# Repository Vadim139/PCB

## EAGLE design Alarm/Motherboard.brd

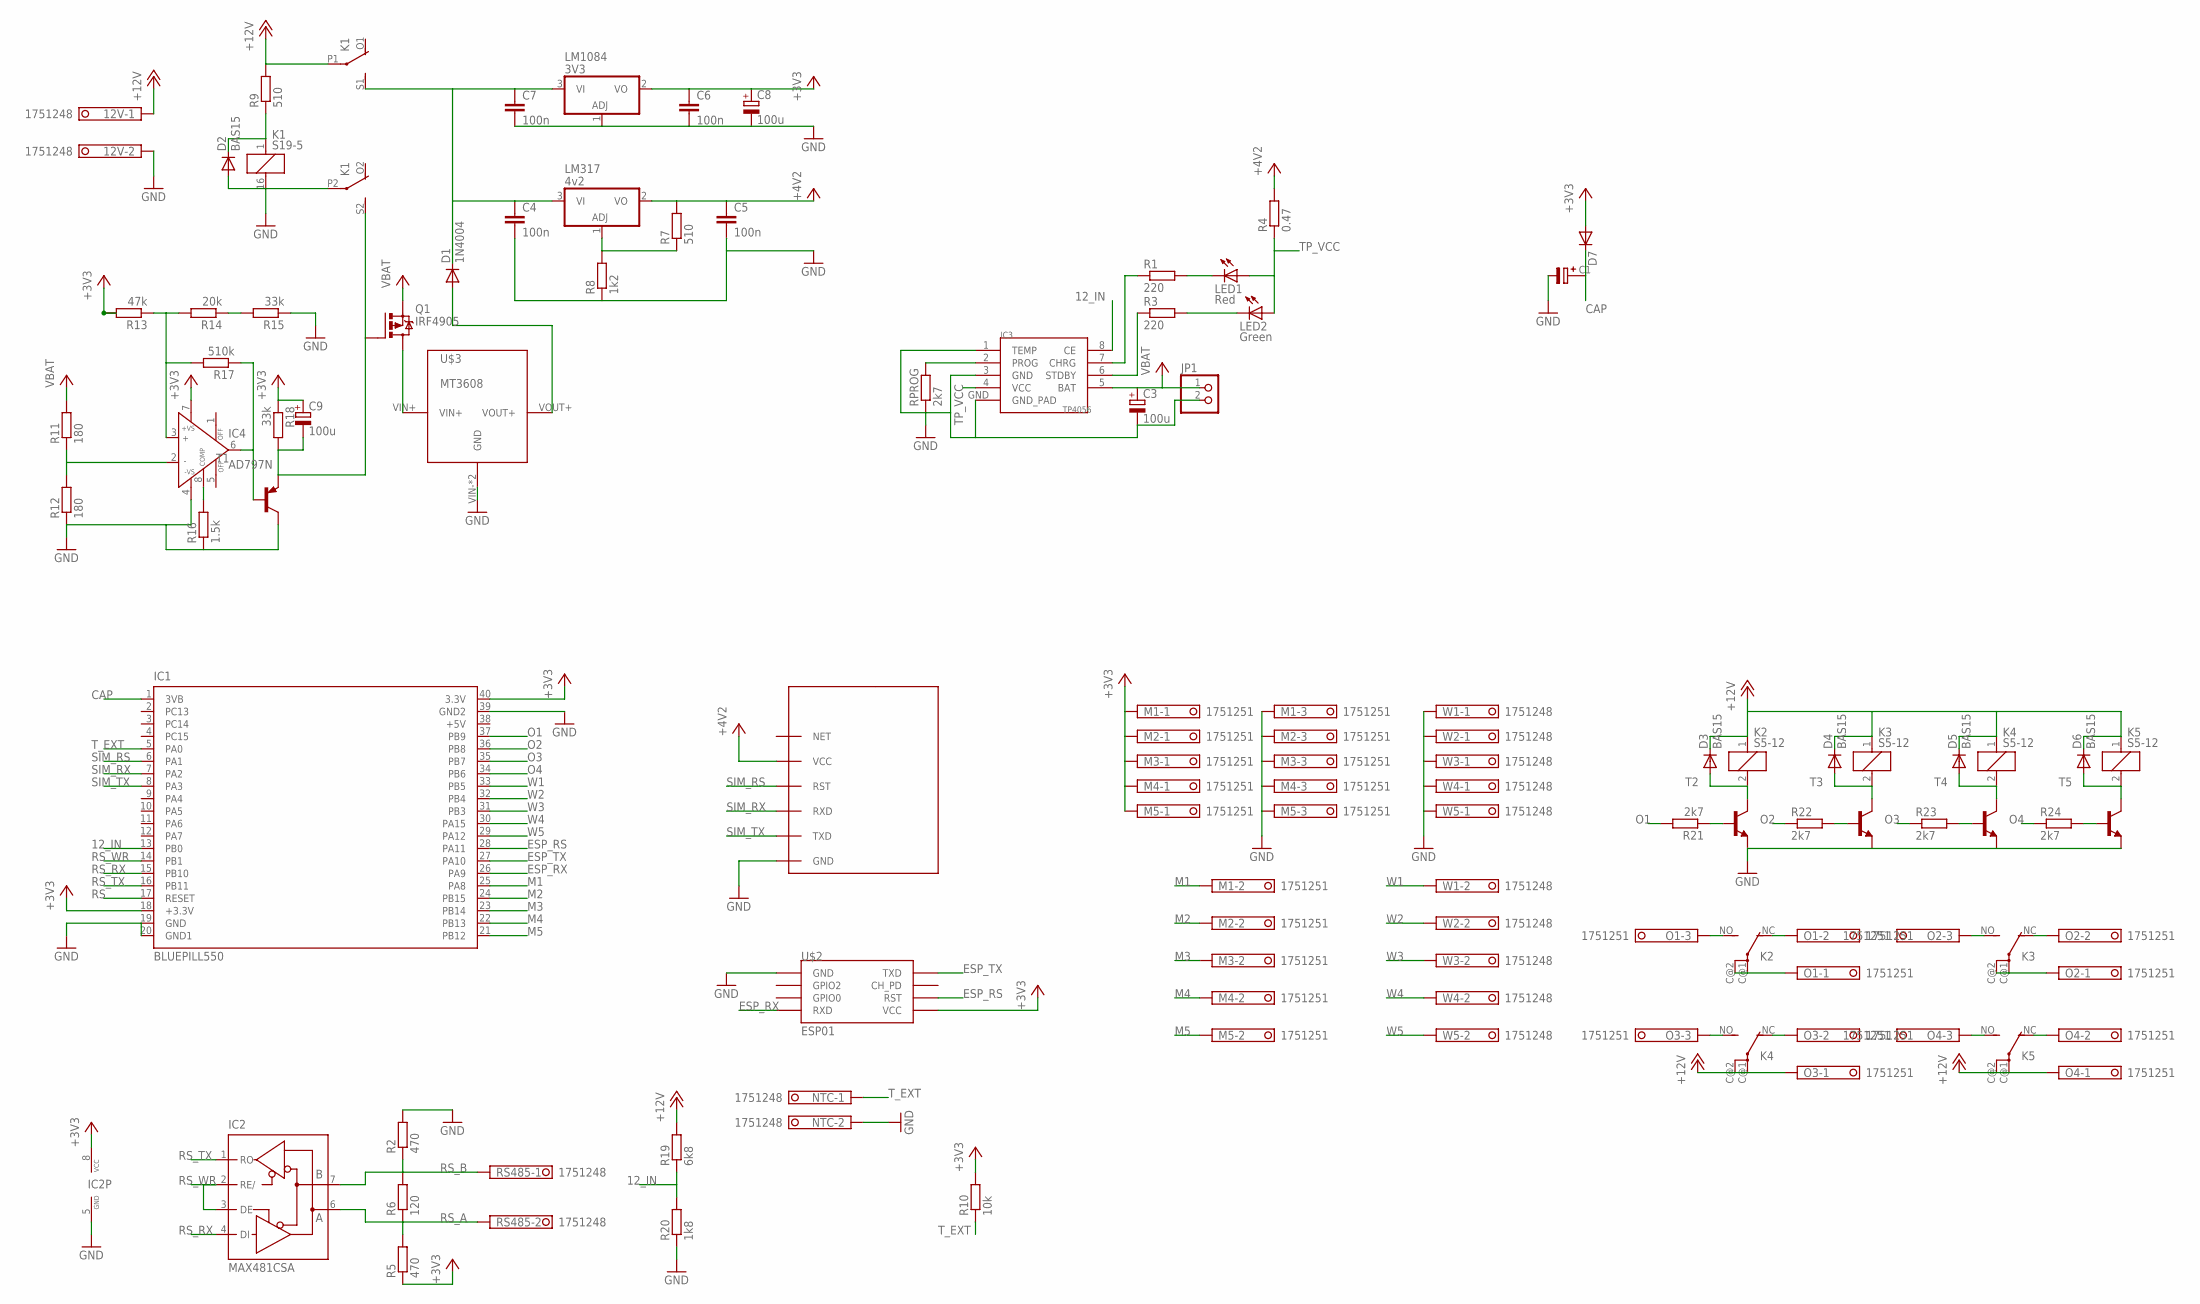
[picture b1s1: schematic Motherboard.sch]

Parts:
12V: 1751248
C1: CAP-13,5; PAC-G-1
C3, C8, C9: 100u; E2,5-6E
C4, C5, C6, C7: 100n; C2012
D1: 1N4004; DO41-10
D2, D3, D4, D5, D6, D7: BAS15; DO34-7
IC1: BLUEPILL550; DIL40
IC2: MAX481CSA; SO08
IC3: TP4056; SOP-8
IC4: AD797N; DIL08
JP1: PINHD-1X2; 1X02
K1: S19-5; 351
K2, K3, K4, K5: S5-12; HY
LED1: Red; CHIP-LED0805
LED2: Green; CHIP-LED0805
LM317: 4v2; TO220H
LM1084: 3V3; TO220H
M1, M2, M3, M4, M5: 1751251
NTC: 1751248
O1, O2, O3, O4: 1751251
Q1: IRF4905; TO220BH
R1, R3: 220; R0805
R2, R5: 470; 0204/5
R4: 0.47; 0207/12
R6: 120; 0204/7
R7, R9: 510; 0204/7
R8: 1k2; 0204/7
R10: 10k; 0204/5
R11, R12: 180; 0204/7
R13: 47k; 0204/7
R14: 20k; 0204/7
R15, R18: 33k; 0204/7
R16: 1.5k; 0204/7
R17: 510k; 0204/7
R19: 6k8; 0204/5
R20: 1k8; 0204/5
R21, R22, R23, R24: 2k7; 0204/7
RPROG: 2k7; 0204/7
RS485: 1751248
T1: BC327-40-PNP-TO92-EBC; TO92-EBC
T2, T3, T4, T5: -NPN-TO92-ECB; TO92-ECB
U$1: SIM800L; SIM-CORE
U$2: ESP01
U$3: MT3608
W1, W2, W3, W4, W5: 1751248

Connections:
4V2: C5.1, LM317.2 (VO), R4.2, R7.2, U$1.VCC
12_IN: IC1.13 (PB0), IC3.8 (CE), R19.1, R20.2
+3V3: C6.1, C8.+, C9.+, D7.A, IC1.18 (+3.3V), IC1.40 (3.3V), IC2.8 (VCC), IC4.7 (+VS), LM1084.2 (VO), M1.1, M2.1, M3.1, M4.1, M5.1, R5.1, R10.2, R13.2, R18.1, U$2.VCC
+12V: 12V.1, D3.C, D4.C, D5.C, D6.C, K1.P1, K2.1, K3.1, K4.1, K4.C@1, K4.C@2, K5.1, K5.C@1, K5.C@2, O3.1, O4.1, R9.2, R19.2
CAP: C1.+, D7.C, IC1.1 (3VB)
ESP_RS: IC1.28 (PA11), U$2.RST
ESP_RX: IC1.26 (PA9), U$2.RX (RXD)
ESP_TX: IC1.27 (PA10), U$2.TX (TXD)
GND: 12V.2, C1.-, C3.-, C4.2, C5.2, C6.2, C7.2, C8.-, D2.A, IC1.19 (GND), IC1.20 (GND1), IC1.39 (GND2), IC2.5 (GND), IC3.1 (TEMP), IC3.3 (GND), IC3.GND (GND_PAD), IC4.4 (-VS), JP1.2, K1.16 (2), K1.P2, LM1084.1 (ADJ), M1.3, M2.3, M3.3, M4.3, M5.3, NTC.2, R2.2, R8.1, R12.1, R15.1, R16.1, R20.1, RPROG.1, T1.C, T2.E, T3.E, T4.E, T5.E, U$1.GND, U$2.GND, U$3.VIN- (GND), U$3.VOUT- (GND), W1.1, W2.1, W3.1, W4.1, W5.1
M1: IC1.25 (PA8), M1.2
M2: IC1.24 (PB15), M2.2
M3: IC1.23 (PB14), M3.2
M4: IC1.22 (PB13), M4.2
M5: IC1.21 (PB12), M5.2
unnamed: IC3.2 (PROG), RPROG.2
unnamed: D2.C, K1.1, R9.1
unnamed: LED1.C, R1.2
unnamed: LED2.C, R3.2
unnamed: IC3.7 (CHRG), R1.1
unnamed: IC3.6 (STDBY), R3.1
unnamed: C4.1, C7.1, D1.C, K1.S1 (S), LM317.3 (VI), LM1084.3 (VI)
unnamed: Q1.D, U$3.VIN+
unnamed: IC4.3 (IN+), R13.1, R14.2, R17.2
unnamed: IC4.2 (IN-), R11.1, R12.2
unnamed: IC4.8 (COMP), R16.2
unnamed: IC4.6 (OUT), R17.1, T1.B
unnamed: LM317.1 (ADJ), R7.1, R8.2
unnamed: C9.-, K1.S2 (S), Q1.G, R18.2, T1.E
unnamed: R24.2, T5.B
unnamed: R23.2, T4.B
unnamed: R22.2, T3.B
unnamed: R21.1, T2.B
unnamed: K4.NO (S), O3.3
unnamed: K4.NC (O), O3.2
unnamed: K5.NO (S), O4.3
unnamed: K5.NC (O), O4.2
unnamed: K2.NO (S), O1.3
unnamed: K2.C@1, K2.C@2, O1.1
unnamed: K2.NC (O), O1.2
unnamed: K3.NO (S), O2.3
unnamed: K3.NC (O), O2.2
unnamed: K3.C@1, K3.C@2, O2.1
unnamed: R14.1, R15.2
unnamed: D6.A, K5.2, T5.C
unnamed: D3.A, K2.2, T2.C
unnamed: D4.A, K3.2, T3.C
unnamed: D5.A, K4.2, T4.C
O1: IC1.37 (PB9), R21.2
O2: IC1.36 (PB8), R22.1
O3: IC1.35 (PB7), R23.1
O4: IC1.34 (PB6), R24.1
PA6: IC1.11 (PA6)
PA7: IC1.12 (PA7)
RS: IC1.17 (RESET)
RS_A: IC2.6 (A), R5.2, R6.1, RS485.2
RS_B: IC2.7 (B), R2.1, R6.2, RS485.1
RS_RX: IC1.15 (PB10), IC2.4 (DI)
RS_TX: IC1.16 (PB11), IC2.1 (RO)
RS_WR: IC1.14 (PB1), IC2.2 (RE/), IC2.3 (DE)
SIM_RS: IC1.6 (PA1), U$1.RST
SIM_RX: IC1.7 (PA2), U$1.RXD
SIM_TX: IC1.8 (PA3), U$1.TXD
TP_VCC: IC3.4 (VCC), LED1.A, LED2.A, R4.1
T_EXT: IC1.5 (PA0), NTC.1, R10.1
VBAT: C3.+, IC3.5 (BAT), JP1.1, Q1.S, R11.2
VOUT+: D1.A, U$3.VOUT+
W1: IC1.33 (PB5), W1.2
W2: IC1.32 (PB4), W2.2
W3: IC1.31 (PB3), W3.2
W4: IC1.30 (PA15), W4.2
W5: IC1.29 (PA12), W5.2

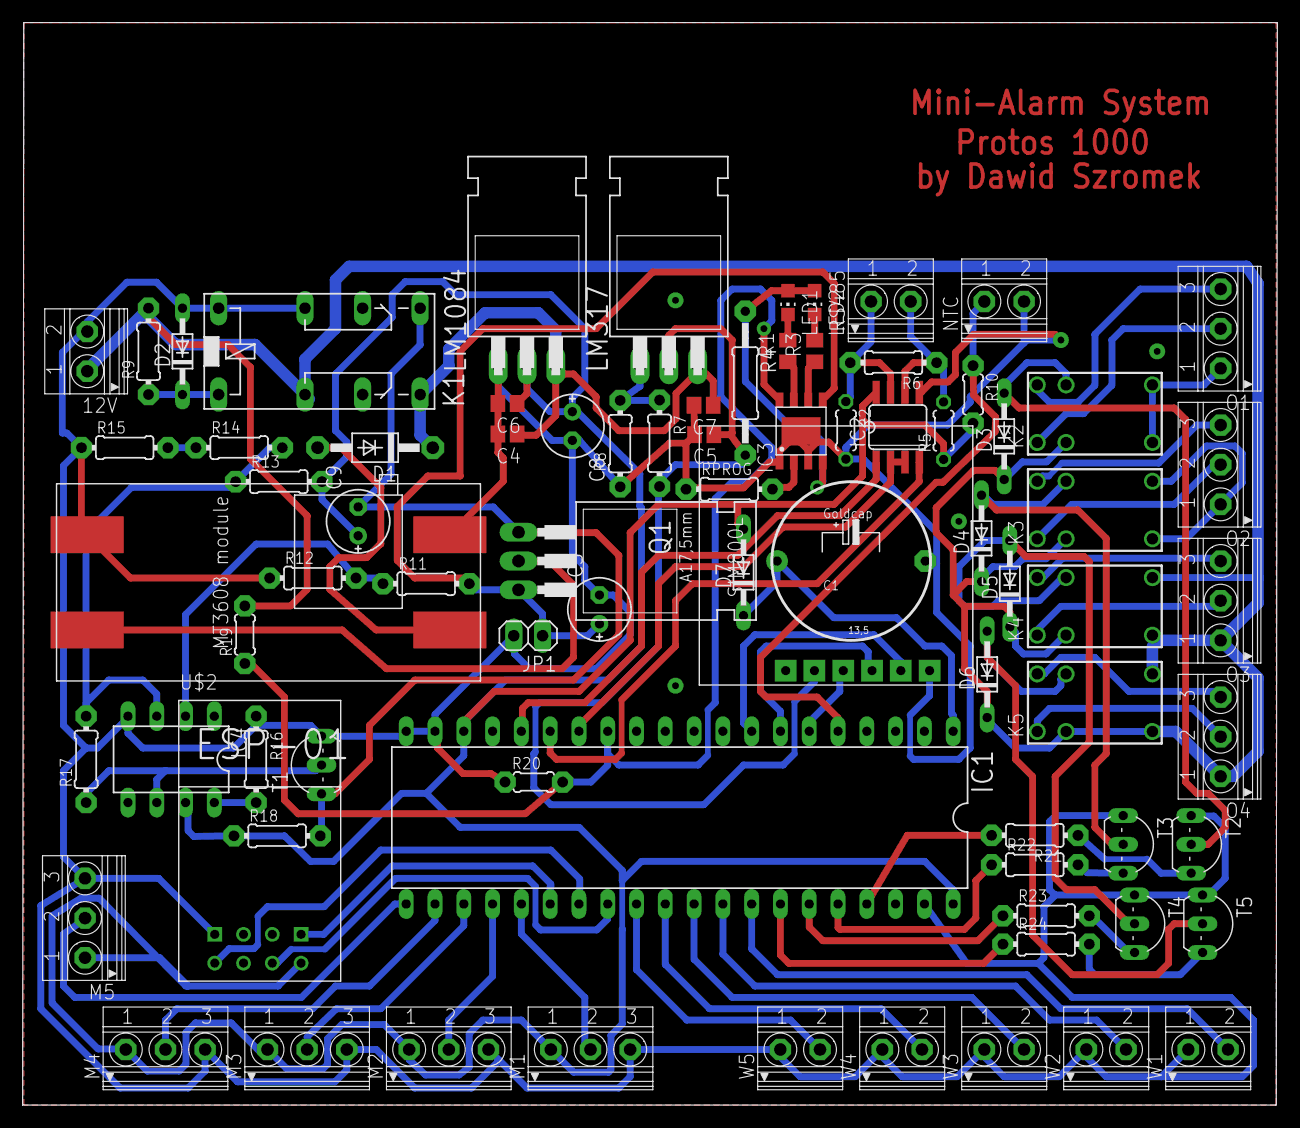
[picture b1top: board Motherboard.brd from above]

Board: 2 copper layers, 110.7 x 95.5 mm, 80 parts (0 on the bottom side), 68 nets.

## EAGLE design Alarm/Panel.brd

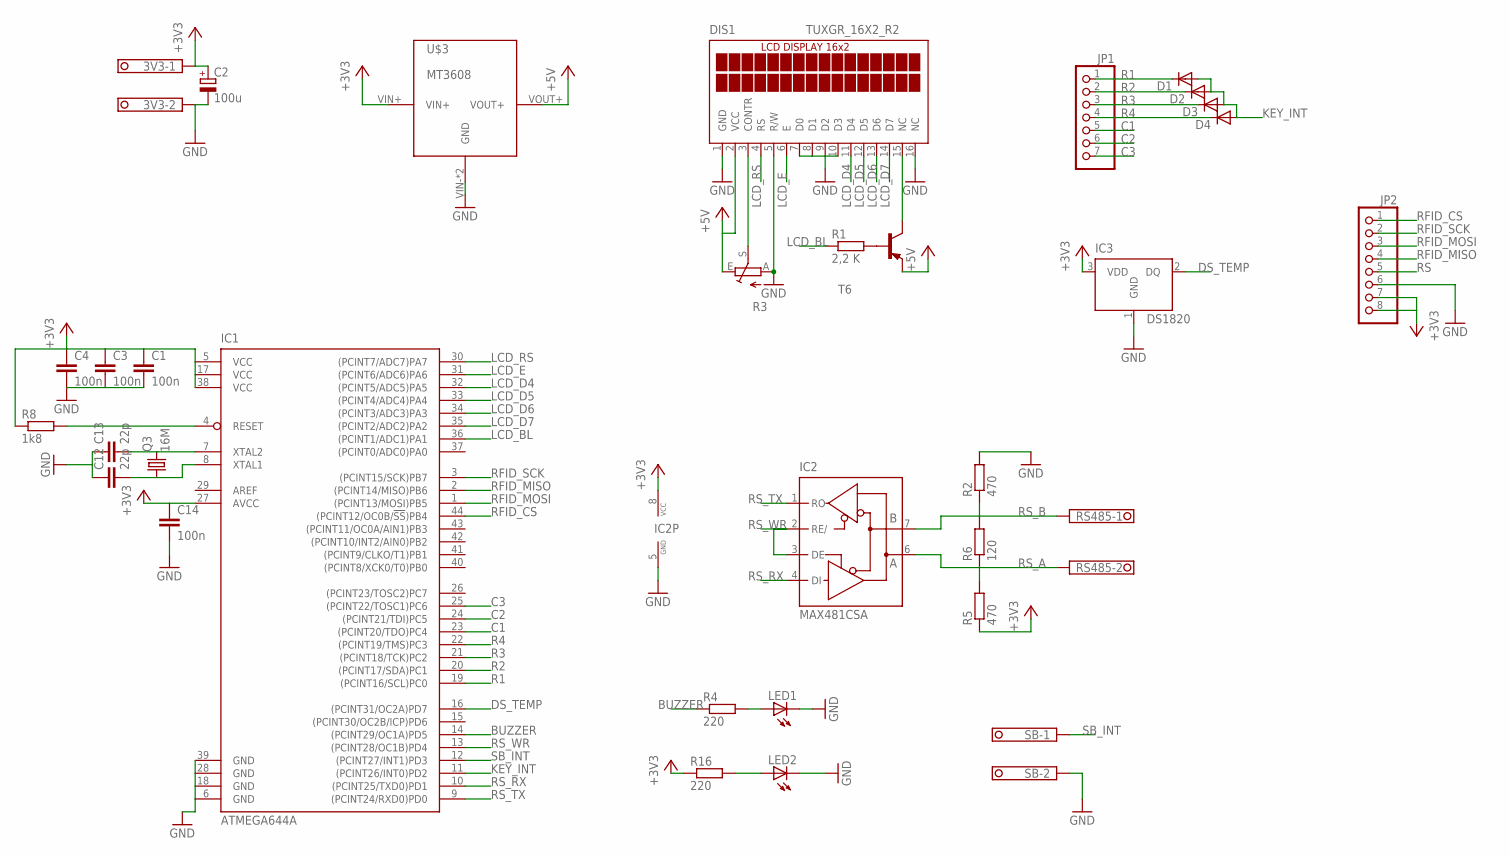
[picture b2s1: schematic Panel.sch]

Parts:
3V3: 1751248
C1, C3, C4, C14: 100n; C2012
C2: 100u; E2,5-6E
C12, C13: 22p; C050-024X044
D1, D2, D3, D4: BAS15; DO34-7
DIS1: TUXGR_16X2_R2
IC1: ATMEGA644A; TQFP44
IC2: MAX481CSA; SO08
IC3: DS1820; TO-92-
JP1: PINHD-1X7; 1X07
JP2: PINHD-1X8; 1X08
LED1, LED2: LED3MM
Q3: 16M; HC49U-V
R1: 2,2 K; 0204/7
R2, R5: 470; 0204/5
R3: TRIM_EU-CA6V; CA6V
R4, R16: 220; 0204/7
R6: 120; 0204/7
R8: 1k8; 0204/7
RS485: 1751248
SB: 1751248
T6: BC327-40-PNP-TO92-EBC; TO92-EBC
U$3: MT3608

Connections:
+3V3: 3V3.1, C1.1, C2.+, C3.1, C4.1, C14.1, IC1.5 (VCC), IC1.17 (VCC), IC1.27 (AVCC), IC1.38 (VCC), IC2.8 (VCC), IC3.3 (VDD), JP2.7, JP2.8, R5.1, R8.1, R16.1, U$3.VIN+
+5V: DIS1.2 (VCC), R3.E, T6.E, U$3.VOUT+
BUZZER: IC1.14 ((PCINT29/OC1A)PD5), R4.1
C1: IC1.23 ((PCINT20/TDO)PC4), JP1.5
C2: IC1.24 ((PCINT21/TDI)PC5), JP1.6
C3: IC1.25 ((PCINT22/TOSC1)PC6), JP1.7
DS_TEMP: IC1.16 ((PCINT31/OC2A)PD7), IC3.2 (DQ)
GND: 3V3.2, C1.2, C2.-, C3.2, C4.2, C12.1, C13.1, C14.2, DIS1.1 (GND), DIS1.5 (R/W), DIS1.7 (D0), DIS1.8 (D1), DIS1.9 (D2), DIS1.10 (D3), DIS1.16 (NC), IC1.6 (GND), IC1.18 (GND), IC1.28 (GND), IC1.39 (GND), IC2.5 (GND), IC3.1 (GND), JP2.6, LED1.K (C), LED2.K (C), R2.2, R3.A, SB.2, U$3.VIN- (GND), U$3.VOUT- (GND)
KEY_INT: D1.A, D2.A, D3.A, D4.A, IC1.11 ((PCINT26/INT0)PD2)
LCD_BL: IC1.36 ((PCINT1/ADC1)PA1), R1.1
LCD_D4: DIS1.11 (D4), IC1.32 ((PCINT5/ADC5)PA5)
LCD_D5: DIS1.12 (D5), IC1.33 ((PCINT4/ADC4)PA4)
LCD_D6: DIS1.13 (D6), IC1.34 ((PCINT3/ADC3)PA3)
LCD_D7: DIS1.14 (D7), IC1.35 ((PCINT2/ADC2)PA2)
LCD_E: DIS1.6 (E), IC1.31 ((PCINT6/ADC6)PA6)
LCD_RS: DIS1.4 (RS), IC1.30 ((PCINT7/ADC7)PA7)
unnamed: C12.2, IC1.8 (XTAL1), Q3.1
unnamed: R1.2, T6.B
unnamed: LED1.A, R4.2
unnamed: C13.2, IC1.7 (XTAL2), Q3.2
unnamed: DIS1.3 (CONTR), R3.S
unnamed: DIS1.15 (NC), T6.C
unnamed: LED2.A, R16.2
R1: D1.C, IC1.19 ((PCINT16/SCL)PC0), JP1.1
R2: D2.C, IC1.20 ((PCINT17/SDA)PC1), JP1.2
R3: D3.C, IC1.21 ((PCINT18/TCK)PC2), JP1.3
R4: D4.C, IC1.22 ((PCINT19/TMS)PC3), JP1.4
RFID_CS: IC1.44 ((PCINT12/OC0B/!SS!)PB4), JP2.1
RFID_MISO: IC1.2 ((PCINT14/MISO)PB6), JP2.4
RFID_MOSI: IC1.1 ((PCINT13/MOSI)PB5), JP2.3
RFID_SCK: IC1.3 ((PCINT15/SCK)PB7), JP2.2
RS: IC1.4 (RESET), JP2.5, R8.2
RS_A: IC2.6 (A), R5.2, R6.1, RS485.2
RS_B: IC2.7 (B), R2.1, R6.2, RS485.1
RS_RX: IC1.10 ((PCINT25/TXD0)PD1), IC2.4 (DI)
RS_TX: IC1.9 ((PCINT24/RXD0)PD0), IC2.1 (RO)
RS_WR: IC1.13 ((PCINT28/OC1B)PD4), IC2.2 (RE/), IC2.3 (DE)
SB_INT: IC1.12 ((PCINT27/INT1)PD3), SB.1

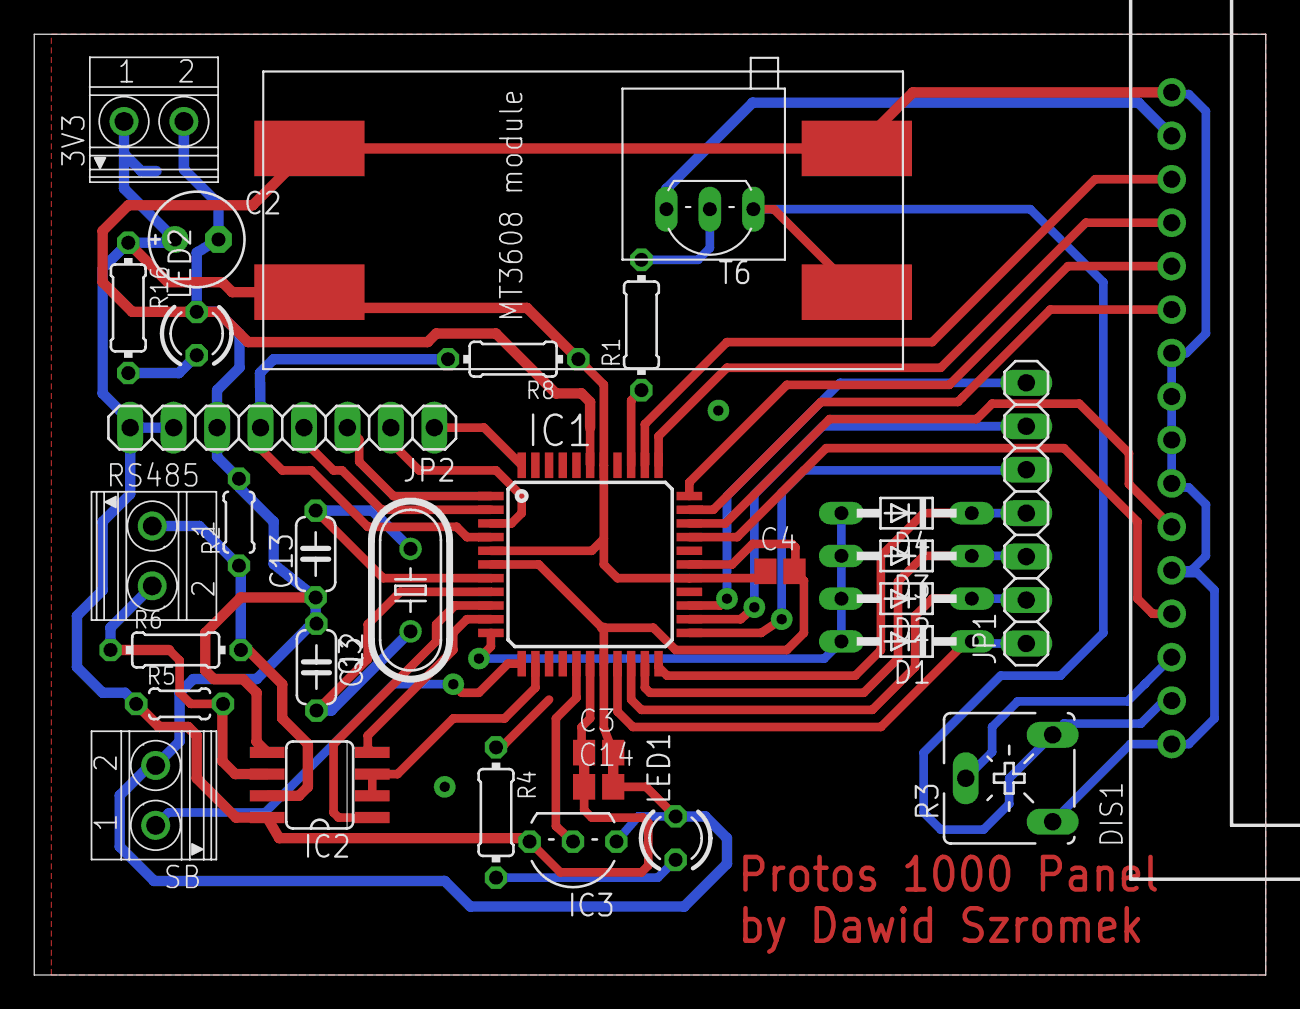
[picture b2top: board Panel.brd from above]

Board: 2 copper layers, 72.0 x 55.0 mm, 33 parts (1 on the bottom side), 38 nets.

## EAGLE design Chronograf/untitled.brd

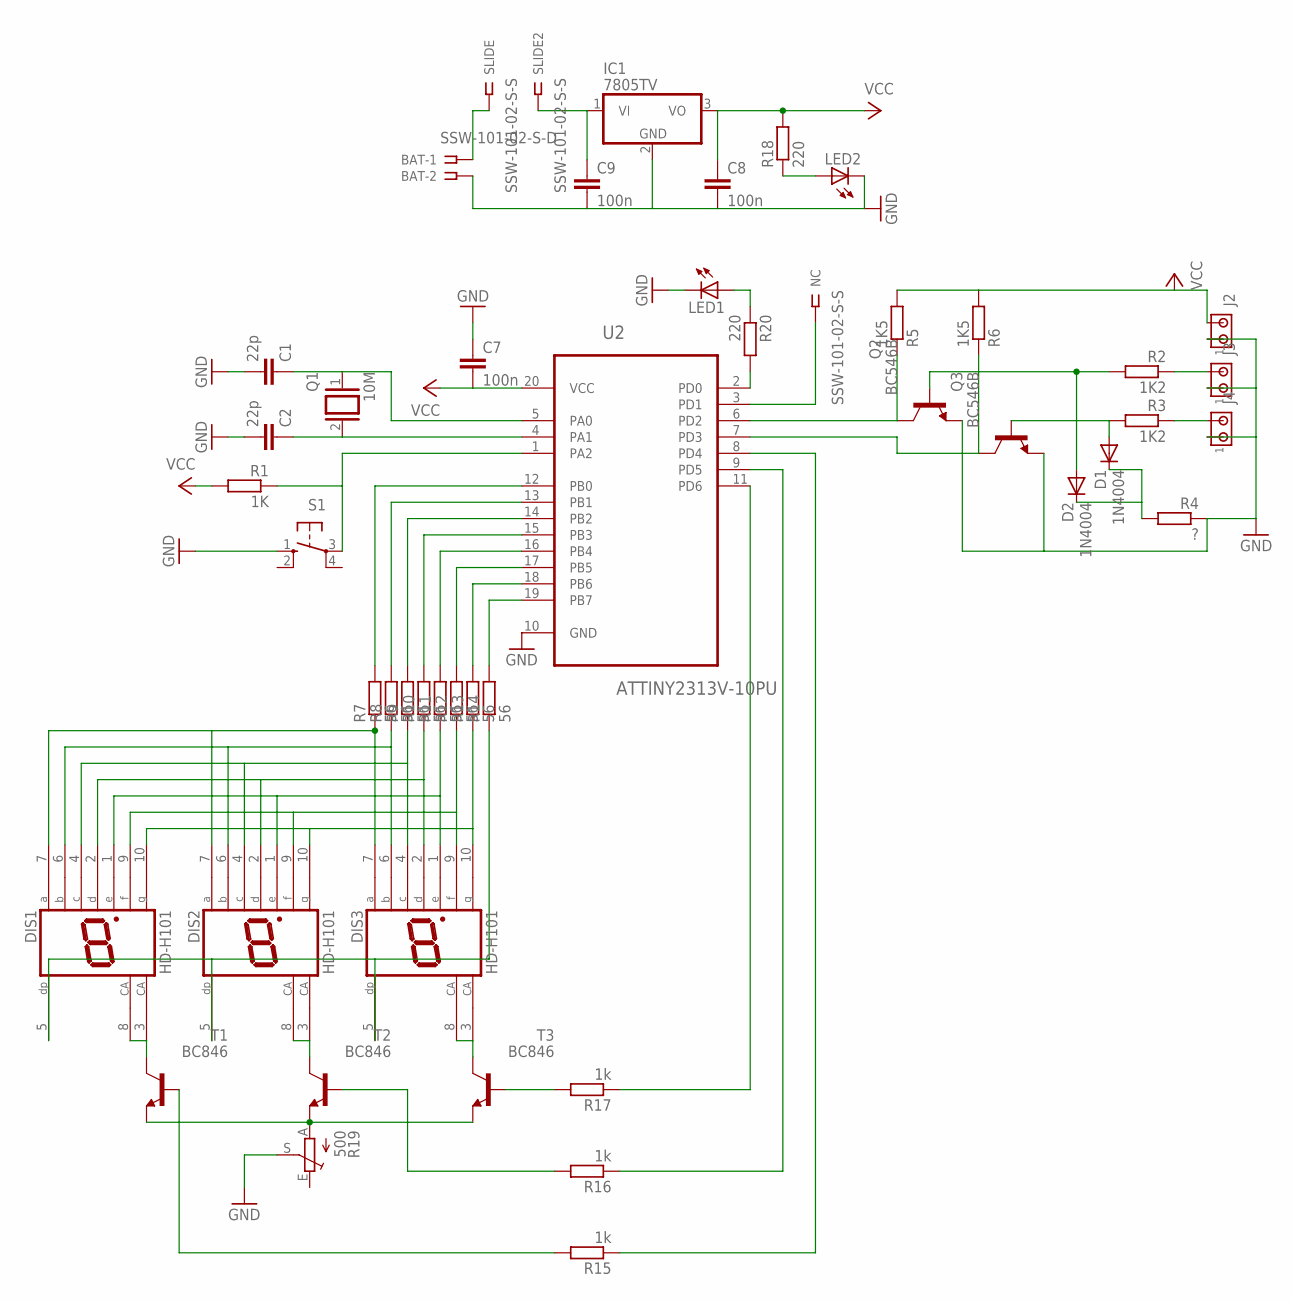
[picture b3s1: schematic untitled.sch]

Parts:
BAT: SSW-101-02-S-D
C1, C2: 22p; C050-024X044
C7, C8, C9: 100n; C1206
D1, D2: 1N4004; DO41-10
DIS1, DIS2, DIS3: HD-H101; HDSP-M
IC1: 7805TV; TO220V
J2, J3, J4: MTA02-100; 10X02MTA
LED1, LED2: LED3MM
NC: SSW-101-02-S-S
Q1: 10M; QS
Q2, Q3: BC546B; TO92-EBC
R1: 1K; 0204/7
R2, R3: 1K2; 0204/7
R4: ?; 0204/7
R5, R6: 1K5; 0204/7
R7, R8, R9, R10, R11, R12, R13, R14: 56; M1206
R15, R16, R17: 1k; M1206
R18, R20: 220; M1206
R19: 500; CA6V
S1: 10-XX; B3F-10XX
SLIDE, SLIDE2: SSW-101-02-S-S
T1, T2, T3: BC846; SOT23
U2: ATTINY2313V-10PU; DIP254P762X533-20

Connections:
GND: BAT.2, C1.2, C2.2, C7.1, C8.2, C9.2, IC1.2 (GND), J2.1, J3.1, J4.1, LED1.K (C), LED2.K (C), Q2.E, Q3.E, R4.1, R19.S, S1.1 (S), U2.10 (GND)
unnamed: C1.1, Q1.1, U2.5 (PA0)
unnamed: DIS1.10 (G), DIS2.10 (G), DIS3.10 (G), R13.1
unnamed: R1.1, S1.3, U2.1 (PA2)
unnamed: R20.2, U2.2 (PD0)
unnamed: C9.1, IC1.1 (VI), SLIDE2.1
unnamed: J3.2, R2.1
unnamed: J4.2, R3.1
unnamed: D2.A, Q2.B, R2.2
unnamed: D1.A, Q3.B, R3.2
unnamed: D1.C, D2.C, R4.2
unnamed: Q3.C, R6.1, U2.7 (PD3)
unnamed: Q2.C, R5.1, U2.6 (PD2)
unnamed: C2.1, Q1.2, U2.4 (PA1)
unnamed: DIS1.9 (F), DIS2.9 (F), DIS3.9 (F), R12.1
unnamed: DIS1.1 (E), DIS2.1 (E), DIS3.1 (E), R11.1
unnamed: DIS1.2 (D), DIS2.2 (D), DIS3.2 (D), R10.1
unnamed: DIS1.4 (C), DIS2.4 (C), DIS3.4 (C), R9.1
unnamed: DIS1.6 (B), DIS2.6 (B), DIS3.6 (B), R8.1
unnamed: DIS1.7 (A), DIS2.7 (A), DIS3.7 (A), R7.1
unnamed: R13.2, U2.18 (PB6)
unnamed: DIS1.5 (DP), DIS2.5 (DP), DIS3.5 (DP), R14.1
unnamed: R12.2, U2.17 (PB5)
unnamed: R11.2, U2.16 (PB4)
unnamed: R10.2, U2.15 (PB3)
unnamed: R9.2, U2.14 (PB2)
unnamed: R8.2, U2.13 (PB1)
unnamed: R7.2, U2.12 (PB0)
unnamed: R14.2, U2.19 (PB7)
unnamed: DIS1.3 (CA), DIS1.8 (CA), T1.3 (C)
unnamed: DIS2.3 (CA), DIS2.8 (CA), T2.3 (C)
unnamed: DIS3.3 (CA), DIS3.8 (CA), T3.3 (C)
unnamed: R19.A, T1.2 (E), T2.2 (E), T3.2 (E)
unnamed: R16.2, T2.1 (B)
unnamed: R17.1, U2.11 (PD6)
unnamed: R16.1, U2.9 (PD5)
unnamed: R15.1, U2.8 (PD4)
unnamed: R15.2, T1.1 (B)
unnamed: R17.2, T3.1 (B)
unnamed: BAT.1, SLIDE.1
unnamed: NC.1, U2.3 (PD1)
unnamed: LED2.A, R18.1
unnamed: LED1.A, R20.1
VCC: C7.2, C8.1, IC1.3 (VO), J2.2, R1.2, R5.2, R6.2, R18.2, U2.20 (VCC)

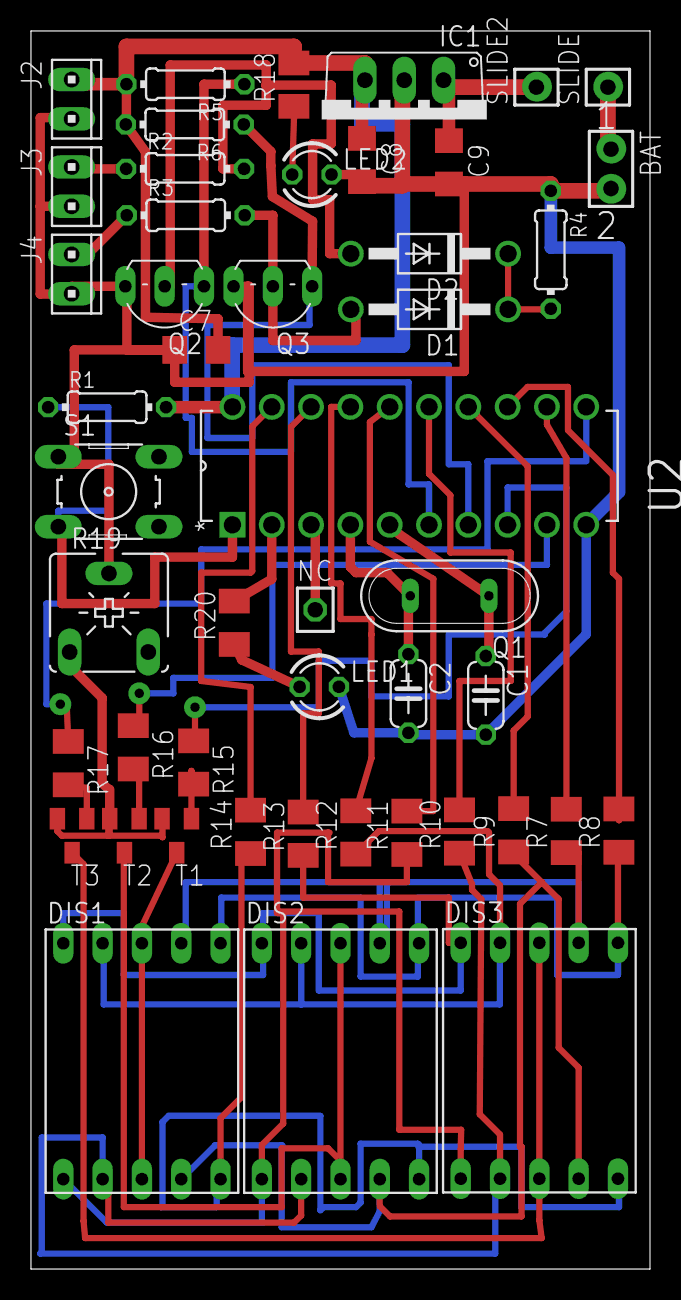
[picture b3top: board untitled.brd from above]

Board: 2 copper layers, 40.0 x 80.0 mm, 48 parts (0 on the bottom side), 44 nets.

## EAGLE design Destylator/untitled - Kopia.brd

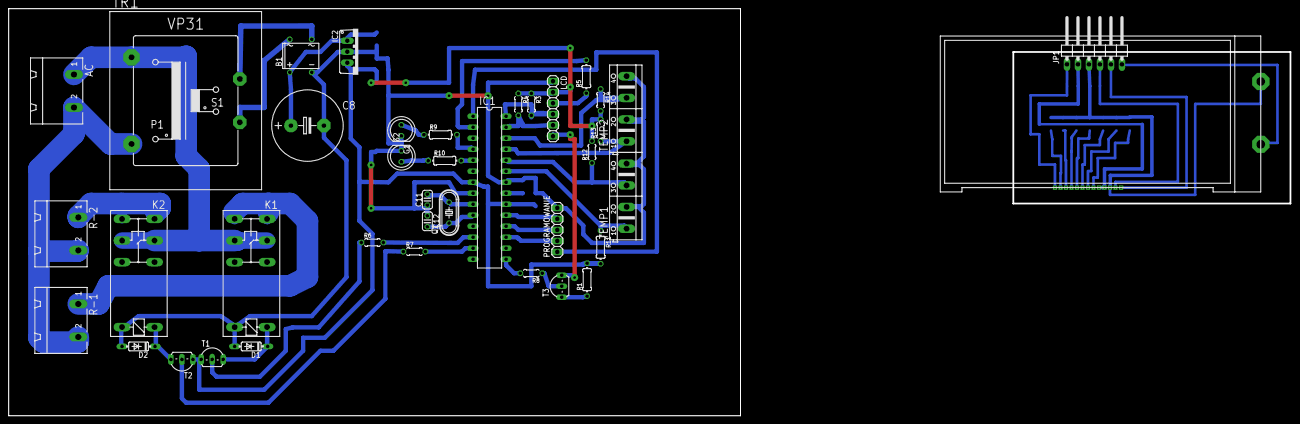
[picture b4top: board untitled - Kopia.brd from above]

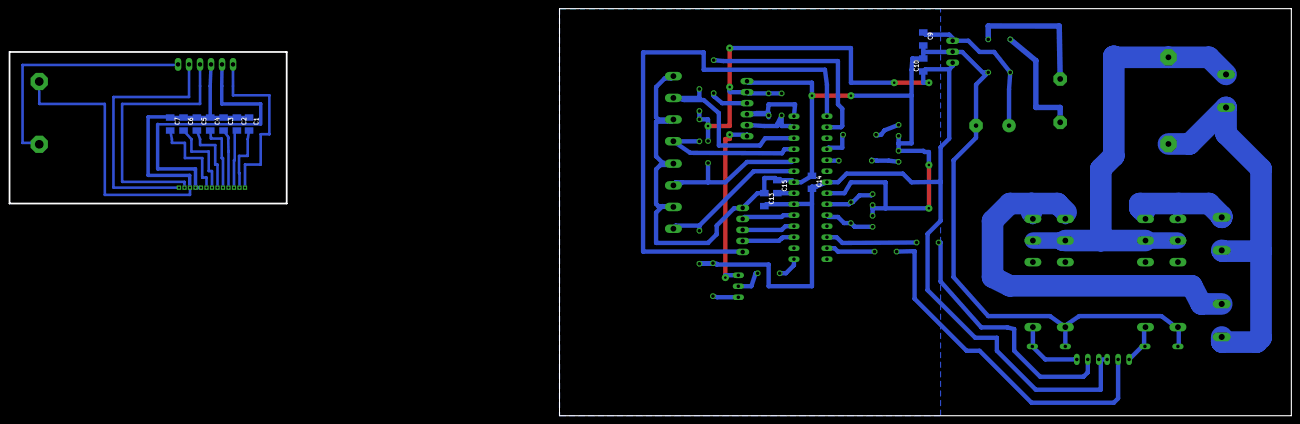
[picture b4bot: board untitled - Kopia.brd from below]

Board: 2 copper layers, 169.0 x 94.0 mm, 51 parts (12 on the bottom side), 51 nets.

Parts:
AC: GMSTBA2
B1: DBL207G; DB
C1, C2, C3, C4, C5, C6, C7, C9, C10, C13, C14, C15: 0,1u; C1206K
C8: 2200u; E7,5-16
C11, C12: C025-024X044
D1, D2: 1N4148DO35-7; DO35-7
G1, G2: LED5MM
IC1: MEGA8-P; DIL28-3
IC2: 7805TV; TO220V
JP1: 1X06/90
K1, K2: G2RE
LCD: 1X06
PROGRAMOWANIE: 1X05
Q1: HC49/S
R1: 33; 0204/7
R3, R4, R6, R7, R8: 1k; 0204/5
R5: 1k; 0204/7
R9, R10: 220; 0204/7
R11: 10k; 0204/7
R12, R13, R14: 10k; 0204/5
R-1, R-2: GMSTBA2
T1, T2, T3: TO92-CBE
TEMP1, TEMP2: AK500/4
TR1: VP31
U$1: RX2004A

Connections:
AC1: AC.1, K1.P0, K1.P1, K2.P0, K2.P1, TR1.1
AC2: AC.2, R-1.2, R-2.2, TR1.2
G1: IC1.12, R6.2
G2: IC1.13, R7.2
GND: B1.-, C8.-, C9.2, C10.2, C11.1, C12.1, C13.1, C14.1, C15.1, D1.A, D2.A, G1.K, G2.K, IC1.8, IC1.22, IC2.2, K1.2, K2.2, LCD.1, PROGRAMOWANIE.5, TEMP1.2, TEMP1.4, TEMP2.2, TEMP2.4
LCDGND: C1.1, C2.1, C3.1, C4.1, C5.1, C6.1, C7.1, JP1.3, U$1.LED-, U$1.P$11
LCDRES: JP1.1, U$1.P$1
LCDVCC: JP1.2, U$1.P$9, U$1.P$10
LCD_SCL: JP1.4, U$1.P$12
LCD_SDA: JP1.5, U$1.P$13
LED+: LCD.6, T3.E
LRES: LCD.3, R5.1
L_LED+: JP1.6, U$1.LED+
MISO: IC1.18, PROGRAMOWANIE.3
MOSI: IC1.17, PROGRAMOWANIE.2
unnamed: C1.2, U$1.P$2
unnamed: C2.2, U$1.P$3
unnamed: C3.2, U$1.P$4
unnamed: C4.2, U$1.P$5
unnamed: C5.2, U$1.P$6
unnamed: C6.2, U$1.P$7
unnamed: C7.2, U$1.P$8
unnamed: K1.S0, K1.S1, R-1.1
unnamed: C11.2, IC1.9, Q1.2
unnamed: B1.AC1, TR1.4
unnamed: B1.AC2, TR1.3
unnamed: C12.2, IC1.10, Q1.1
unnamed: B1.+, C8.+, C9.1, IC2.1
unnamed: C15.2, IC1.21
unnamed: K2.S0, K2.S1, R-2.1
unnamed: R1.1, T3.C
unnamed: R6.1, T1.B
unnamed: R8.1, T3.B
unnamed: R7.1, T2.B
unnamed: D2.C, K2.1, T2.E
unnamed: IC1.4, R9.2
unnamed: IC1.5, R10.2
unnamed: D1.C, K1.1, T1.E
unnamed: G1.A, R9.1
unnamed: G2.A, R10.1
unnamed: IC1.2, R5.2
RES: IC1.1, PROGRAMOWANIE.1
SCK: IC1.19, PROGRAMOWANIE.4
SCL: IC1.28, LCD.4, R3.2
SDA: IC1.27, LCD.5, R4.2
T1_IN: IC1.23, R11.1, TEMP1.1
T2_IN: IC1.24, R12.1, TEMP1.3
T3_IN: IC1.25, R13.1, TEMP2.1
T4_IN: IC1.26, R14.1, TEMP2.3
TLED+: IC1.15, R8.2
VCC: C10.1, C13.2, C14.2, IC1.7, IC1.20, IC2.3, LCD.2, R1.2, R3.1, R4.1, R11.2, R12.2, R13.2, R14.2, T1.C, T2.C

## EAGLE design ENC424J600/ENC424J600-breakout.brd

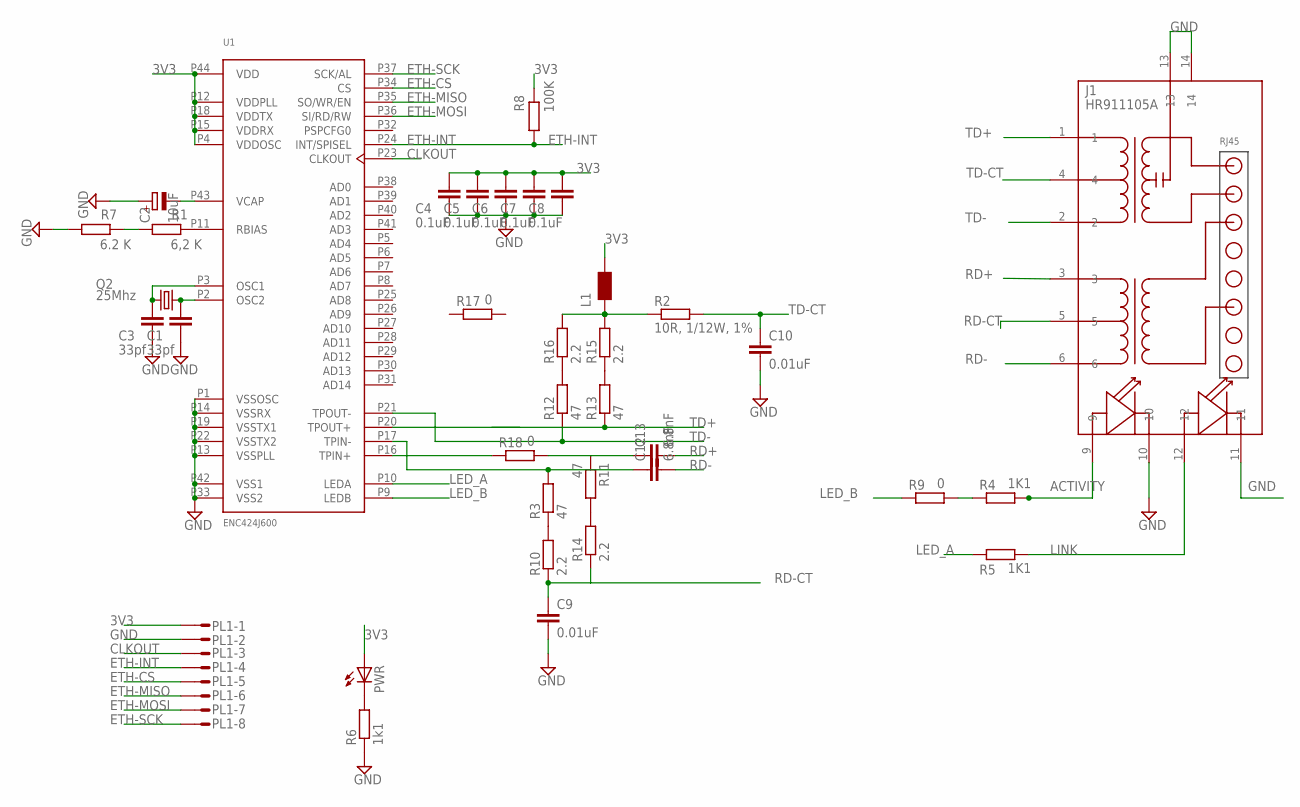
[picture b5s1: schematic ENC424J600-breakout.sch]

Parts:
C1, C3: 33pf; C050-024X044
C2: 10uF; E2,5-5
C4, C5, C6, C7, C8: 0.1uF; C050-024X044
C9: 0.01uF; C050-030X075
C10: 0.01uF; C050-025X075
C12, C13: 6.8nF; C050-024X044
J1: HR911105A
L1: WE-KIL_0805; WE-KI_0805_B
PL1: 10VS; 10V
PWR: LED805; LED-805
Q2: 25Mhz; HC49U70
R1: 6,2 K; 0207/7
R2: 10R, 1/12W, 1%; 0207/7
R3, R11, R12, R13: 47; 0207/7
R4, R5: 1K1; 0204/5
R6: 1k1; 0204/5
R7: 6.2 K; 0207/7
R8: 100K; 0207/7
R9, R17, R18: 0; 0204/5
R10, R14, R15, R16: 2.2; 0207/7
U1: ENC424J600; TQFP44

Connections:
3V3: C4.1, C5.1, C6.1, C7.1, C8.1, L1.1 (2), PL1.1, PWR.A, R8.1, U1.P4 (VDDOSC), U1.P12 (VDDPLL), U1.P15 (VDDRX), U1.P18 (VDDTX), U1.P44 (VDD)
ACTIVITY: J1.9, R4.2
CCT: L1.2 (1), R2.1, R15.2, R16.2
CLKOUT: PL1.3, U1.P23 (CLKOUT)
DSFGDF: C12.1, R3.2, U1.P17 (TPIN-)
DSGDFSG: C13.1, R11.1, R18.2
ETH-CS: PL1.5, U1.P34 (CS)
ETH-INT: PL1.4, R8.2, U1.P24 (INT/SPISEL)
ETH-MISO: PL1.6, U1.P35 (SO/WR/EN)
ETH-MOSI: PL1.7, U1.P36 (SI/RD/RW)
ETH-SCK: PL1.8, U1.P37 (SCK/AL)
GND: C1.2, C2.+, C3.2, C4.2, C5.2, C6.2, C7.2, C8.2, C9.2, C10.2, J1.10, J1.11, J1.13, J1.14, PL1.2, R6.1, R7.2, U1.P1 (VSSOSC), U1.P13 (VSSPLL), U1.P14 (VSSRX), U1.P19 (VSSTX1), U1.P22 (VSSTX2), U1.P33 (VSS2), U1.P42 (VSS1)
LED_A: R5.1, U1.P10 (LEDA)
LED_B: R9.1, U1.P9 (LEDB)
LINK: J1.12, R5.2
unnamed: C2.-, U1.P43 (VCAP)
unnamed: R1.1, U1.P11 (RBIAS)
unnamed: PWR.C, R6.2
unnamed: C3.1, Q2.1, U1.P3 (OSC1)
unnamed: R1.2, R7.1
unnamed: R3.1, R10.2
unnamed: R11.2, R14.2
unnamed: C1.1, Q2.2, U1.P2 (OSC2)
unnamed: R13.2, R15.1
unnamed: R12.2, R16.1
unnamed: R4.1, R9.2
unnamed: R18.1, U1.P16 (TPIN+)
RD+: C13.2, J1.3
RD-: C12.2, J1.6
RD-CT: C9.1, J1.5, R10.1, R14.1
TD+: J1.1, R13.1, U1.P20 (TPOUT+)
TD-: J1.2, R12.1, U1.P21 (TPOUT-)
TD-CT: C10.1, J1.4, R2.2

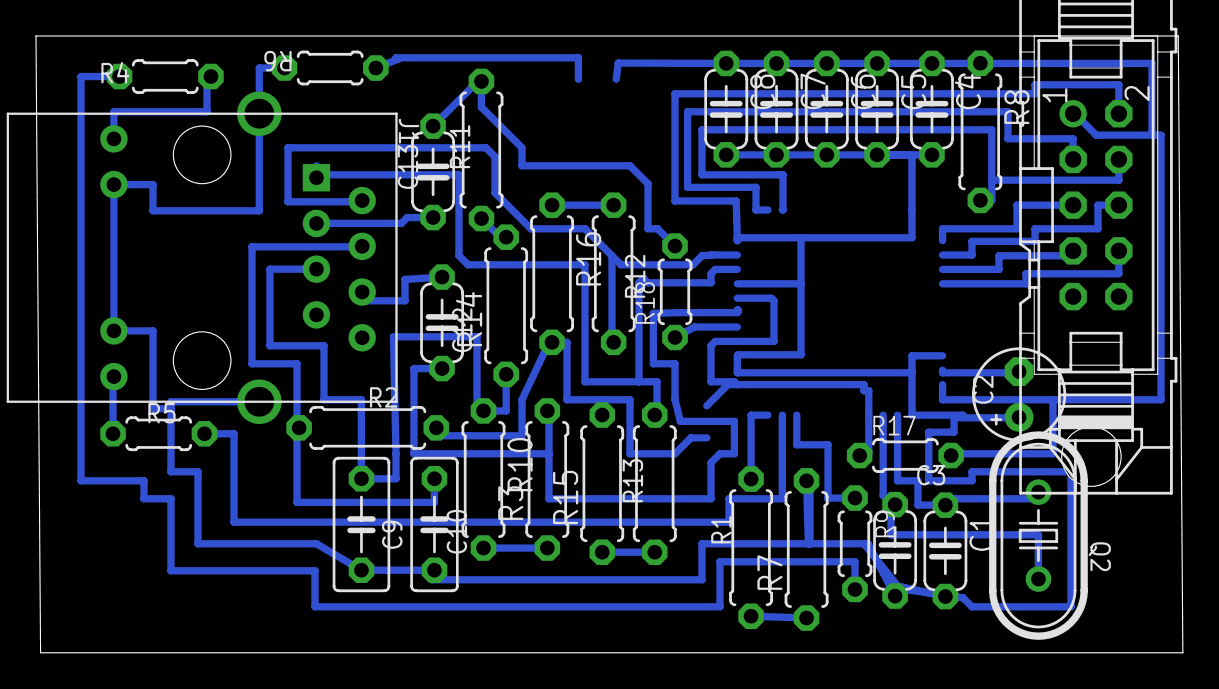
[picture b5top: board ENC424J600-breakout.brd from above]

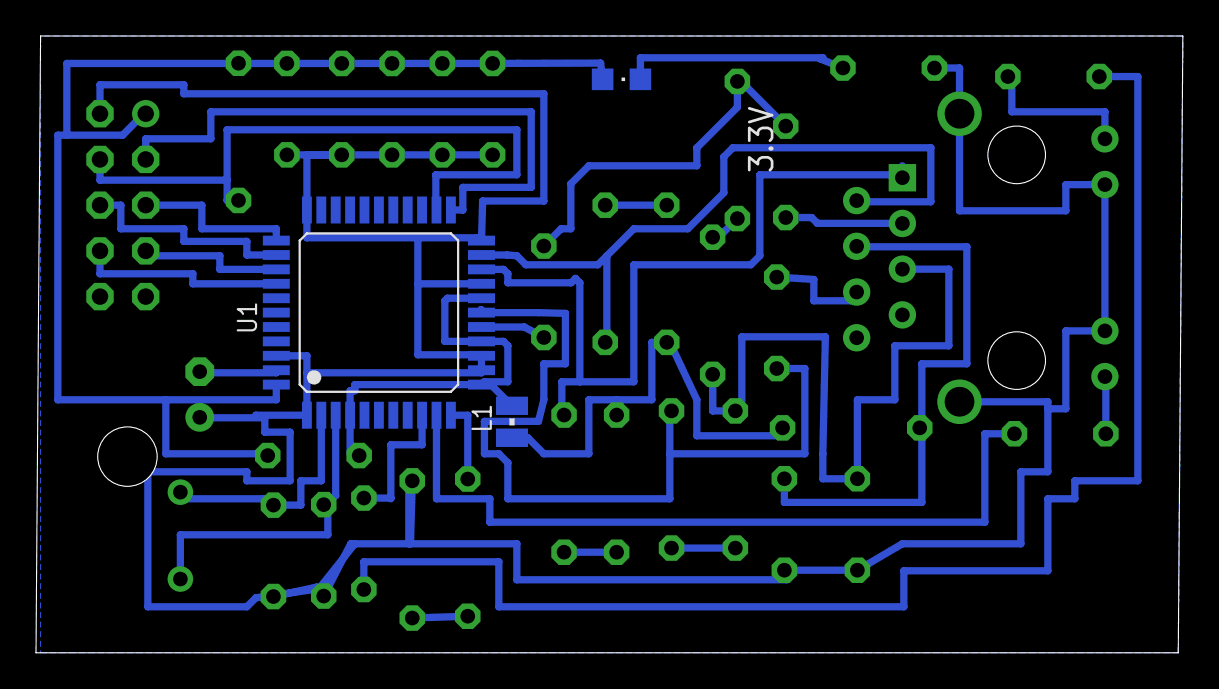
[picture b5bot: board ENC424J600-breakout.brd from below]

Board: 2 copper layers, 63.7 x 34.3 mm, 36 parts (3 on the bottom side), 33 nets.
